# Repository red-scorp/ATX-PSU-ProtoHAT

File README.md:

# ATX-PSU-ProtoHAT project

ATX-PSU-ProtoHAT project test HAT board for ATX PSU.

## ATX-PSU-ProtoHAT

**ATX-PSU-ProtoHAT** is a prototyping HAT board for DIY use.
This board features Raspberry Pi and ATX PSU connector.

Preview:

[Schematics in PDF format](doc/ATX-PSU-ProtoHAT.pdf)

Features:

- Raspberry Pi 40-pin connector
- ATX PSU 24-pin connector
- DIY raster DOT area for prototyping

CAM files are available.

## Version History

### v1.1

- Fixed board geomery to fit better to Rasperry Pi HAT spec
- Added few more DIY raster lines
- Fixed typo in pad's description
- Moved texts around

### v1.0

Initial release

## Links

- [pinout.xyz](https://pinout.xyz/) - a brilliant resource on topic of Pi's pinout and HATs.
- [raspberrypi/hats](https://github.com/raspberrypi/hats) - Raspberry Pi HAT specification.
- [Wikipedia:ATX](https://en.wikipedia.org/wiki/ATX) - lengthy decription of ATX standard, including PSU pinout.

## How to help

Your contributions as code, resources, or finances are welcome! Please contact me directly via email at andriy.golovnya@gmail.com or through my [GitHub profile](https://github.com/red-scorp).

If you'd like to make a financial contribution, you can donate via [PayPal](http://paypal.me/redscorp) or [Ko-Fi](http://ko-fi.com/redscorp). Your support is greatly appreciated.

Thanks in advance!

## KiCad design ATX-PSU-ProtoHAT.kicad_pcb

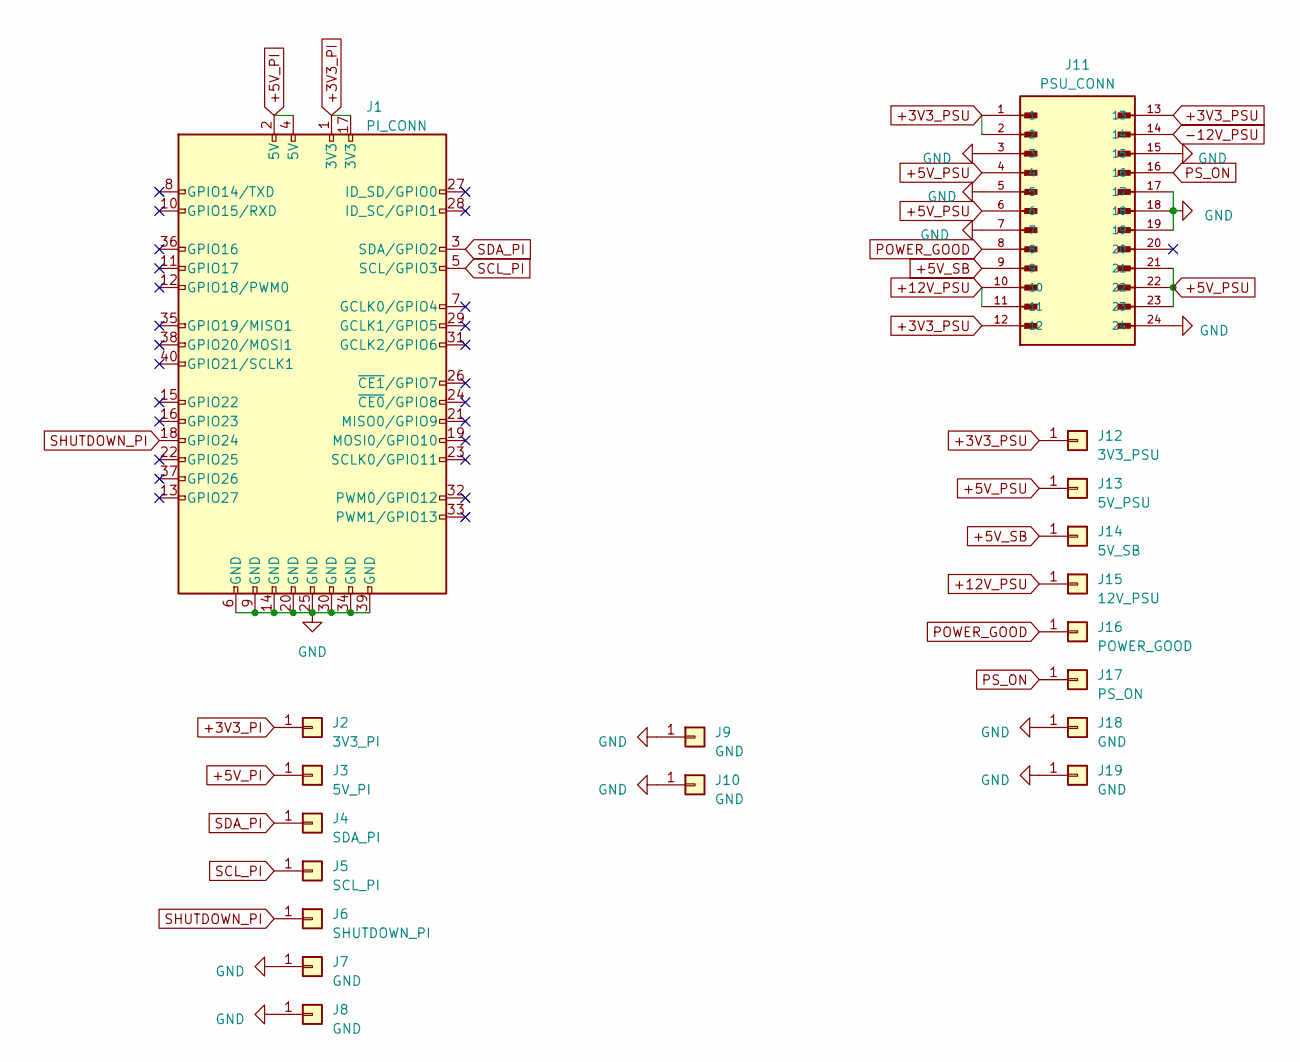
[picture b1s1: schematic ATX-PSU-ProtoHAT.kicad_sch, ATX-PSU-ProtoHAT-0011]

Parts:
J1: PI_CONN; PinSocket_2x20_P2.54mm_Vertical
J2: 3V3_PI; PinHeader_1x01_P2.54mm_Vertical
J3: 5V_PI; PinHeader_1x01_P2.54mm_Vertical
J4: SDA_PI; PinHeader_1x01_P2.54mm_Vertical
J5: SCL_PI; PinHeader_1x01_P2.54mm_Vertical
J6: SHUTDOWN_PI; PinHeader_1x01_P2.54mm_Vertical
J7, J8, J9, J10, J18, J19: GND; PinHeader_1x01_P2.54mm_Vertical
J11: PSU_CONN; MOLEX_462071024; PARTREV C5
J12: 3V3_PSU; PinHeader_1x01_P2.54mm_Vertical
J13: 5V_PSU; PinHeader_1x01_P2.54mm_Vertical
J14: 5V_SB; PinHeader_1x01_P2.54mm_Vertical
J15: 12V_PSU; PinHeader_1x01_P2.54mm_Vertical
J16: POWER_GOOD; PinHeader_1x01_P2.54mm_Vertical
J17: PS_ON; PinHeader_1x01_P2.54mm_Vertical

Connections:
+3V3_PI: J1.1 (3V3), J1.17 (3V3), J2.1
+3V3_PSU: J11.1, J11.2, J11.12, J11.13, J12.1
+5V_PI: J1.2 (5V), J1.4 (5V), J3.1
+5V_PSU: J11.4, J11.6, J11.21, J11.22, J11.23, J13.1
+5V_SB: J11.9, J14.1
+12V_PSU: J11.10, J11.11, J15.1
-12V_PSU: J11.14
GND: J1.6 (GND), J1.9 (GND), J1.14 (GND), J1.20 (GND), J1.25 (GND), J1.30 (GND), J1.34 (GND), J1.39 (GND), J7.1, J8.1, J9.1, J10.1, J11.3, J11.5, J11.7, J11.15, J11.17, J11.18, J11.19, J11.24, J18.1, J19.1
POWER_GOOD: J11.8, J16.1
PS_ON: J11.16, J17.1
SCL_PI: J1.5 (SCL/GPIO3), J5.1
SDA_PI: J1.3 (SDA/GPIO2), J4.1
SHUTDOWN_PI: J1.18 (GPIO24), J6.1

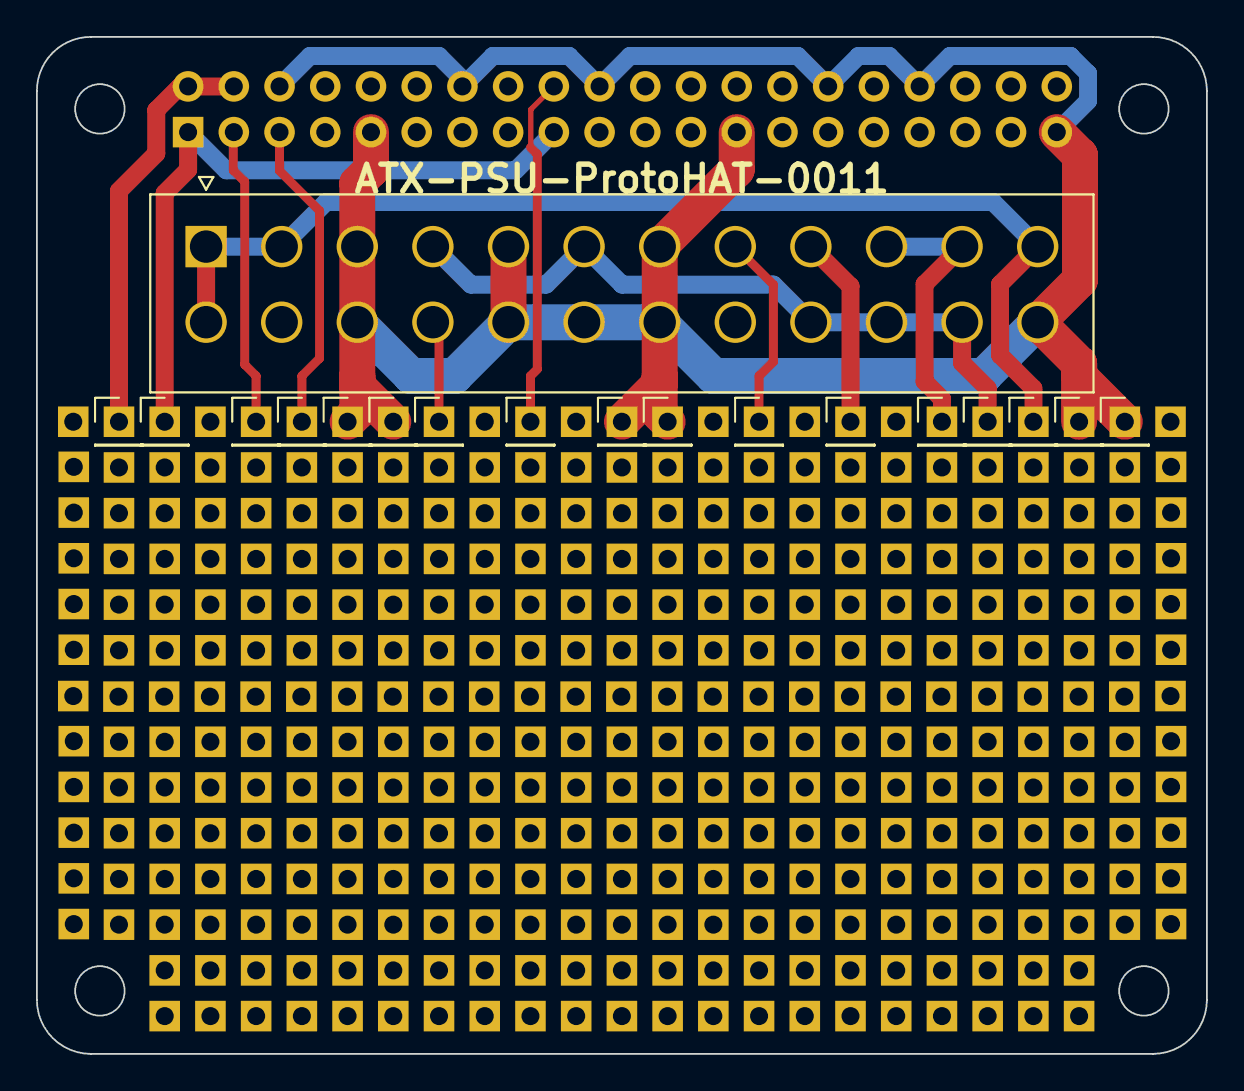
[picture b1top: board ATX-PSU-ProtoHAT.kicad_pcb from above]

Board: 2 copper layers, 65.0 x 56.5 mm, 19 parts (1 on the bottom side), 12 nets.

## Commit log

2023-05-07 Added base of ATX-PSU-ProtoHAT
2023-05-07 Removed measures from Edge.Cuts player.
2023-05-07 Generated CAM files.
2023-05-07 Fixed folder name.
2023-05-07 Added 2 images
2023-05-08 Generated PDF schematics
2023-05-08 Added README.md file
2023-05-08 Renamed images
2023-05-08 Renamed images back
2023-05-08 Fixed ATX PSU connector type
2023-05-27 Typo fixed
2023-05-28 Fixed board geometry to fit Raspberry Pi HAT spec better
2023-05-28 Fixed export directory
2023-05-28 Moved stuff around
2023-05-28 Generated PNG preview
2023-05-28 Generated CAM files
2023-05-28 Increased version number to 1.1
2023-06-01 Fixed board outline
2023-07-12 Added FUNDING.yml

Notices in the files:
ATX-PSU-ProtoHAT.kicad_pcb:
(c) 2023 Andriy Golovnya
